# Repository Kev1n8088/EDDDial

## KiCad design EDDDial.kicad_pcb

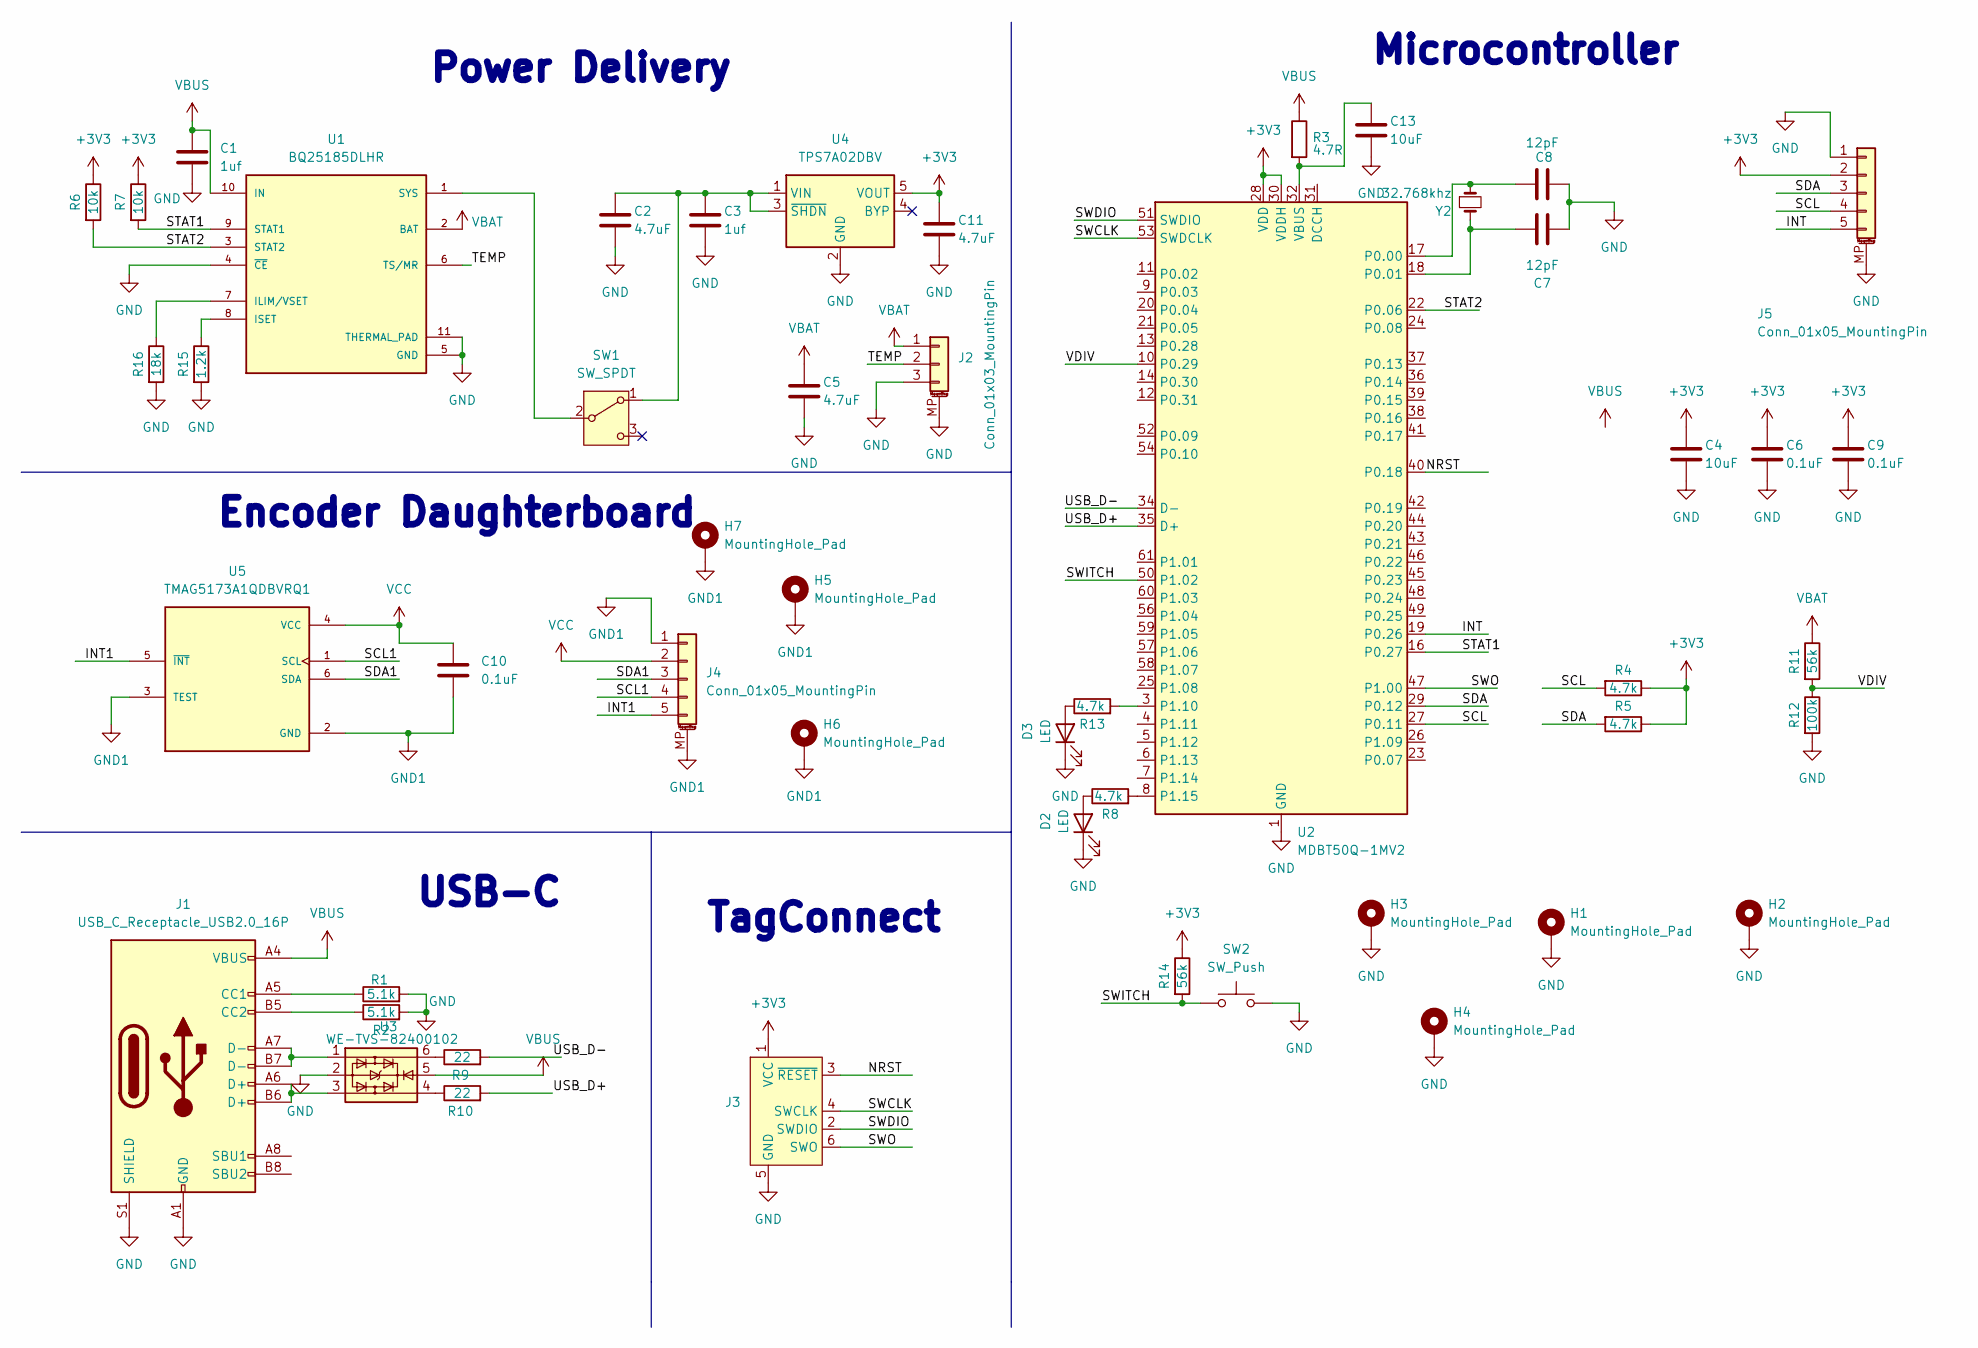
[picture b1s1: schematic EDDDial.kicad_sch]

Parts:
C1, C3: 1uf; C_0402_1005Metric
C2, C5, C11: 4.7uF; C_0402_1005Metric
C4, C13: 10uF; C_0402_1005Metric
C6, C9, C10: 0.1uF; C_0402_1005Metric
C7, C8: 12pF; C_0402_1005Metric
D2, D3: LED; LED_0603_1608Metric
H1, H2, H3, H4, H5, H6, H7: MountingHole_Pad; MountingHole_2.2mm_M2_DIN965_Pad
J1: USB_C_Receptacle_USB2.0_16P; USB_C_Receptacle_GCT_USB4110
J2: Conn_01x03_MountingPin; JST_SH_SM03B-SRSS-TB_1x03-1MP_P1.00mm_Horizontal
J3: Conn_ARM_SWD_TagConnect_TC2030-NL; Tag-Connect_TC2030-IDC-NL_2x03_P1.27mm_Vertical
J4, J5: Conn_01x05_MountingPin; JST_SH_SM05B-SRSS-TB_1x05-1MP_P1.00mm_Horizontal
R1, R2: 5.1k; R_0402_1005Metric
R3: 4.7R; R_0805_2012Metric
R4, R5, R8, R13: 4.7k; R_0402_1005Metric
R6, R7: 10k; R_0402_1005Metric
R9, R10: 22; R_0402_1005Metric
R11, R14: 56k; R_0402_1005Metric
R12: 100k; R_0402_1005Metric
R15: 1.2k; R_0402_1005Metric
R16: 18k; R_0402_1005Metric
SW1: SW_SPDT; SW_E-Switch_EG1271_SPDT
SW2: SW_Push; SW_Push_1P1T_NO_CK_KSC6xxG
U1: BQ25185DLHR; IC_BQ25185DLHR; PARTREV OCTOBER 2023
U2: MDBT50Q-1MV2; Raytac_MDBT50Q
U3: WE-TVS-82400102; SOT-23-6
U4: TPS7A02DBV; TSOT-23-5
U5: TMAG5173A1QDBVRQ1; SOT-23-6; PARTREV A
Y2: 32.768khz; Crystal_SMD_2012-2Pin_2.0x1.2mm

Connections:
+3V3: C4.1, C6.1, C9.1, C11.1, J3.1 (VCC), J5.2, R4.1, R5.1, R6.1, R7.1, R14.1, U2.28 (VDD), U2.30 (VDDH), U4.5 (VOUT)
/INT: J5.5, U2.19 (P0.26)
/INT1: J4.5, U5.5 (~INT)
/NRST: J3.3 (~RESET), U2.40 (P0.18)
/SCL: J5.4, R4.2, U2.27 (P0.11)
/SCL1: J4.4, U5.1 (SCL)
/SDA: J5.3, R5.2, U2.29 (P0.12)
/SDA1: J4.3, U5.6 (SDA)
/STAT1: R7.2, U1.9 (STAT1), U2.16 (P0.27)
/STAT2: R6.2, U1.3 (STAT2), U2.22 (P0.06)
/SWCLK: J3.4 (SWCLK), U2.53 (SWDCLK)
/SWDIO: J3.2 (SWDIO), U2.51 (SWDIO)
/SWITCH: R14.2, SW2.1, U2.50 (P1.02)
/SWO: J3.6 (SWO), U2.47 (P1.00)
/TEMP: J2.2, U1.6 (TS/MR)
/USB_D+: R10.2, U2.35 (D+)
/USB_D-: R9.2, U2.34 (D-)
/VDIV: R11.2, R12.1, U2.10 (P0.29)
GND: C1.2, C2.2, C3.2, C4.2, C5.2, C6.2, C7.1, C8.1, C9.2, C11.2, C13.2, D2.1 (K), D3.1 (K), H1.1, H2.1, H3.1, H4.1, J1.A1 (GND), J1.A12 (GND), J1.B1 (GND), J1.B12 (GND), J1.S1 (SHIELD), J2.3, J2.MP (MountPin), J3.5 (GND), J5.1, J5.MP (MountPin), R1.2, R2.2, R12.2, R15.2, R16.2, SW2.2, U1.4 (~CE), U1.5 (GND), U1.11 (THERMAL_PAD), U2.1 (GND), U2.2 (GND), U2.15 (GND), U2.33 (GND), U2.55 (GND), U3.2, U4.2 (GND)
GND1: C10.2, H5.1, H6.1, H7.1, J4.1, J4.MP (MountPin), U5.2 (GND), U5.3 (TEST)
unnamed: D2.2 (A), R8.1
unnamed: D3.2 (A), R13.1
unnamed: J1.A5 (CC1), R1.1
unnamed: J1.B5 (CC2), R2.1
unnamed: J1.A6 (D+), J1.B6 (D+), U3.3
unnamed: J1.A7 (D-), J1.B7 (D-), U3.1
unnamed: R9.1, U3.6
unnamed: R10.1, U3.4
unnamed: SW1.2 (B), SW1.5 (4), U1.1 (SYS)
unnamed: C2.1, C3.1, SW1.1 (A), SW1.4 (C), U4.1 (VIN), U4.3 (~SHDN)
unnamed: R16.1, U1.7 (ILIM/VSET)
unnamed: R15.1, U1.8 (ISET)
unnamed: C8.2, U2.17 (P0.00), Y2.1
unnamed: C7.2, U2.18 (P0.01), Y2.2
unnamed: R13.2, U2.3 (P1.10)
unnamed: R8.2, U2.8 (P1.15)
unnamed: C13.1, R3.2, U2.32 (VBUS)
VBAT: C5.1, J2.1, R11.1, U1.2 (BAT)
VBUS: C1.1, J1.A4 (VBUS), J1.A9 (VBUS), J1.B4 (VBUS), J1.B9 (VBUS), R3.1, U1.10 (IN), U3.5
VCC: C10.1, J4.2, U5.4 (VCC)

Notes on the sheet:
Power Delivery
TagConnect
Microcontroller
USB-C
Encoder Daughterboard

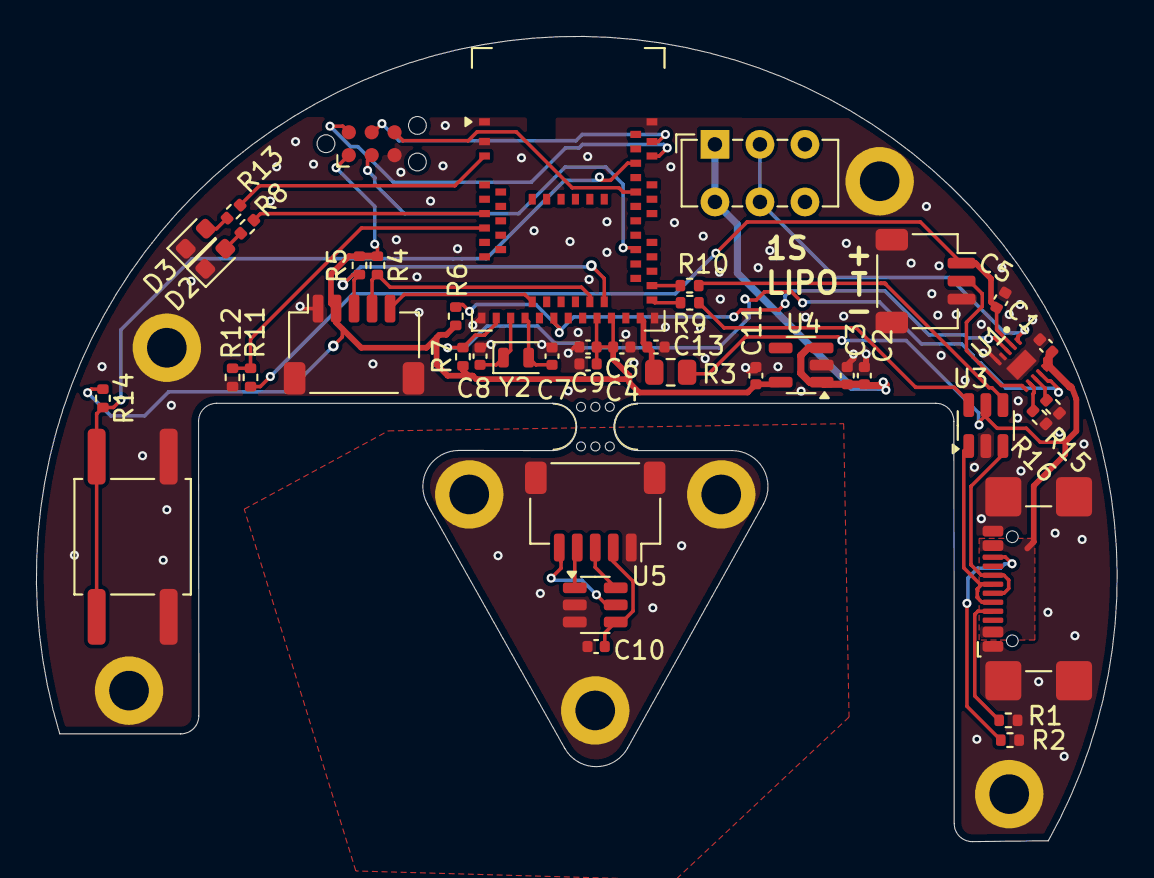
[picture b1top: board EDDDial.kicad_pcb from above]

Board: 2 copper layers, 60.0 x 44.7 mm, 51 parts (0 on the bottom side), 40 nets.

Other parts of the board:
mouse-bite-2.54mm-slot: VAL**; mouse-bite-2.54mm-slot

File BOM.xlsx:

Id | Designator | Footprint | Quantity | Designation | Supplier and ref | Column1 | _1
1 | R13,R4,R5,R8 | R_0402_1005Metric | 4 | 4.7k | RC0402FR-074K7L
2 | R2,R1 | R_0402_1005Metric | 2 | 5.1k | RC0402FR-075K1L
3 | C2,C5,C11 | C_0402_1005Metric | 3 | 4.7uF | CL05A475MO5NUNC
4 | Y2 | Crystal_SMD_2012-2Pin_2.0x1.2mm | 1 | 32.768khz | MU01260-32.768K
5 | C7,C8 | C_0402_1005Metric | 2 | 12pF | GJM1555C1H120FB01D
6 | J2 | JST_SH_SM03B-SRSS-TB_1x03-1MP_P1.00mm_Horizontal | 1 | Conn_01x03_MountingPin | SM03B-SRSS-TB
7 | J4,J5 | JST_SH_SM05B-SRSS-TB_1x05-1MP_P1.00mm_Horizontal | 2 | Conn_01x05_MountingPin | SM05B-SRSS-TB
8 | C13,C4 | C_0402_1005Metric | 2 | 10uF | CL05A106MP5NUNC
9 | R11,R14 | R_0402_1005Metric | 2 | 56k | RC0402FR-0756KL
10 | R12 | R_0402_1005Metric | 1 | 100k | RC0402FR-07100KL
11 | D2 | LED_0402_1005Metric | 1 | LED | QBLP595-IB
12 | D3 | LED_0402_1005Metric | 1 | LED | QBLP595-R5-2897
13 | R16 | R_0402_1005Metric | 1 | 18k | RC0402FR-0718KL
14 | R3 | R_0805_2012Metric | 1 | 4.7R | RC0402FR-074R7L
15 | C9,C10,C6 | C_0402_1005Metric | 3 | 0.1uF | GCM155R71H104KE02D
16 | C1,C3 | C_0402_1005Metric | 2 | 1uf | GRM155R61E105KA12D
17 | SW2 | SW_Push_1P1T_NO_CK_KSC6xxG | 1 | SW_Push | Y31A21055FPLFS
18 | U1 | IC_BQ25185DLHR | 1 | BQ25185DLHR | BQ25185DLHR
19 | J1 | USB_C_Receptacle_GCT_USB4110 | 1 | USB_C_Receptacle_USB2.0_16P | USB4110-GF-A
20 | R7,R6 | R_0402_1005Metric | 2 | 10k | RC0402FR-0710KL
21 | U2 | Raytac_MDBT50Q | 1 | MDBT50Q-1MV2 | MDBT50Q-1MV2
22 | R10,R9 | R_0402_1005Metric | 2 | 22 | RC0402FR-0722RL
23 | U4 | TSOT-23-5 | 1 | TPS7A02DBV | TPS7A0233DBVR
24 | R15 | R_0402_1005Metric | 1 | 1.2k | RC0402FR-071K2L
25 | SW1 | SW_E-Switch_EG1271_SPDT | 1 | SW_SPDT | EG1271
26 | U5 | SOT-23-6 | 1 | TMAG5173A1QDBVRQ1 | TMAG5173A1QDBVRQ1
27 | U3 | SOT-23-6 | 1 | WE-TVS-82400102 | 82400102

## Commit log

2025-12-04 first commit, switching to SOC module
2025-12-05 primary design done, may change some minor things
2025-12-05 Updated to be 60mm dia and completed basic routing
2025-12-09 made 2 layer
2026-03-20 produced device
